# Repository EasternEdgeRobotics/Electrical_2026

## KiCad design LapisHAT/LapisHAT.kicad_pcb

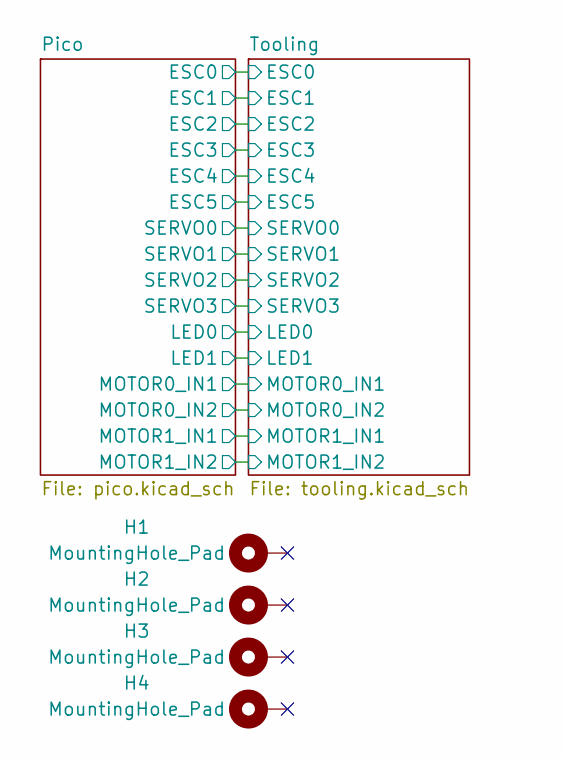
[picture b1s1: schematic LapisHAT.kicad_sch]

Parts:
H1, H2, H3, H4: MountingHole_Pad; MountingHole_3.2mm_M3_Pad_Via

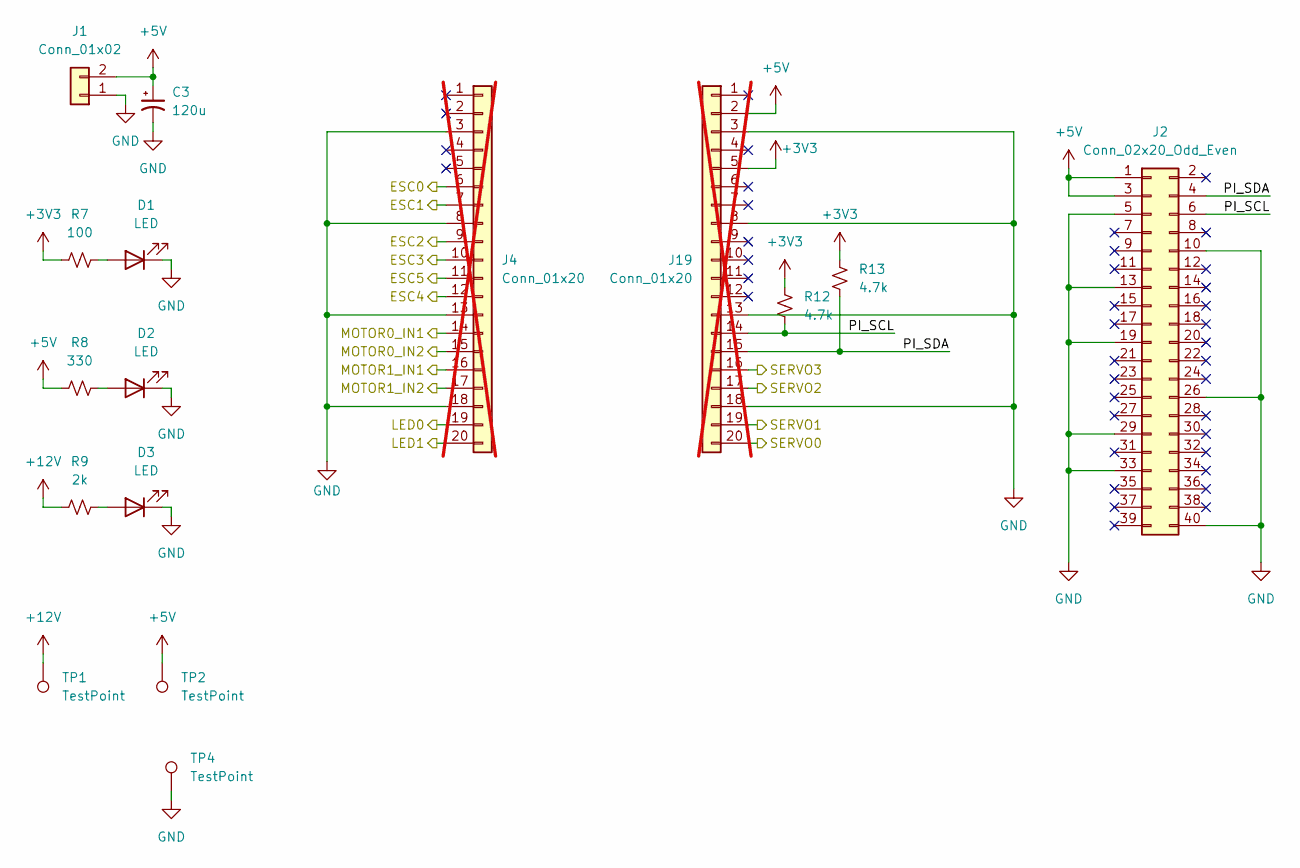
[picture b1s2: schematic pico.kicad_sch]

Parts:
C3: 120u; CP_Elec_10x12.6; LCSC C24725845
D1: LED; LED_0603_1608Metric; LCSC C12065
D2: LED; LED_0603_1608Metric; LCSC C99290
D3: LED; LED_0603_1608Metric; LCSC C94869
J1: Conn_01x02; Molex_Micro-Fit_3.0_43650-0200_1x02_P3.00mm_Horizontal; LCSC C192562
J2: Conn_02x20_Odd_Even; PinHeader_2x20_P2.54mm_Vertical
J4, J19: Conn_01x20; PinHeader_1x20_P2.54mm_Vertical; not fitted
R7: 100; R_0603_1608Metric; LCSC C22775
R8: 330; R_0603_1608Metric; LCSC C23138
R9: 2k; R_0603_1608Metric; LCSC C22975
R12, R13: 4.7k; R_0603_1608Metric; LCSC C23162
TP1, TP2, TP4: TestPoint; TestPoint_Pad_2.0x2.0mm

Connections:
+3V3: J19.5, R7.1, R12.1, R13.1; also elsewhere on the board
+5V: C3.1, J1.2, J2.1, J2.3, J19.2, R8.1, TP2.1; also elsewhere on the board
+12V: R9.1, TP1.1; also elsewhere on the board
/Pico/ESC0: J4.6; also elsewhere on the board
/Pico/ESC1: J4.7; also elsewhere on the board
/Pico/ESC2: J4.9; also elsewhere on the board
/Pico/ESC3: J4.10; also elsewhere on the board
/Pico/ESC4: J4.12; also elsewhere on the board
/Pico/ESC5: J4.11; also elsewhere on the board
/Pico/LED0: J4.19; also elsewhere on the board
/Pico/LED1: J4.20; also elsewhere on the board
/Pico/MOTOR0_IN1: J4.14; also elsewhere on the board
/Pico/MOTOR0_IN2: J4.15; also elsewhere on the board
/Pico/MOTOR1_IN1: J4.16; also elsewhere on the board
/Pico/MOTOR1_IN2: J4.17; also elsewhere on the board
/Pico/PI_SCL: J2.6, J19.14, R12.2
/Pico/PI_SDA: J2.4, J19.15, R13.2
/Pico/SERVO0: J19.20; also elsewhere on the board
/Pico/SERVO1: J19.19; also elsewhere on the board
/Pico/SERVO2: J19.17; also elsewhere on the board
/Pico/SERVO3: J19.16; also elsewhere on the board
GND: C3.2, D1.1 (K), D2.1 (K), D3.1 (K), J1.1, J2.5, J2.10, J2.13, J2.19, J2.26, J2.29, J2.33, J2.40, J4.3, J4.8, J4.13, J4.18, J19.3, J19.8, J19.13, J19.18, TP4.1; also elsewhere on the board
unnamed: D1.2 (A), R7.2
unnamed: D2.2 (A), R8.2
unnamed: D3.2 (A), R9.2

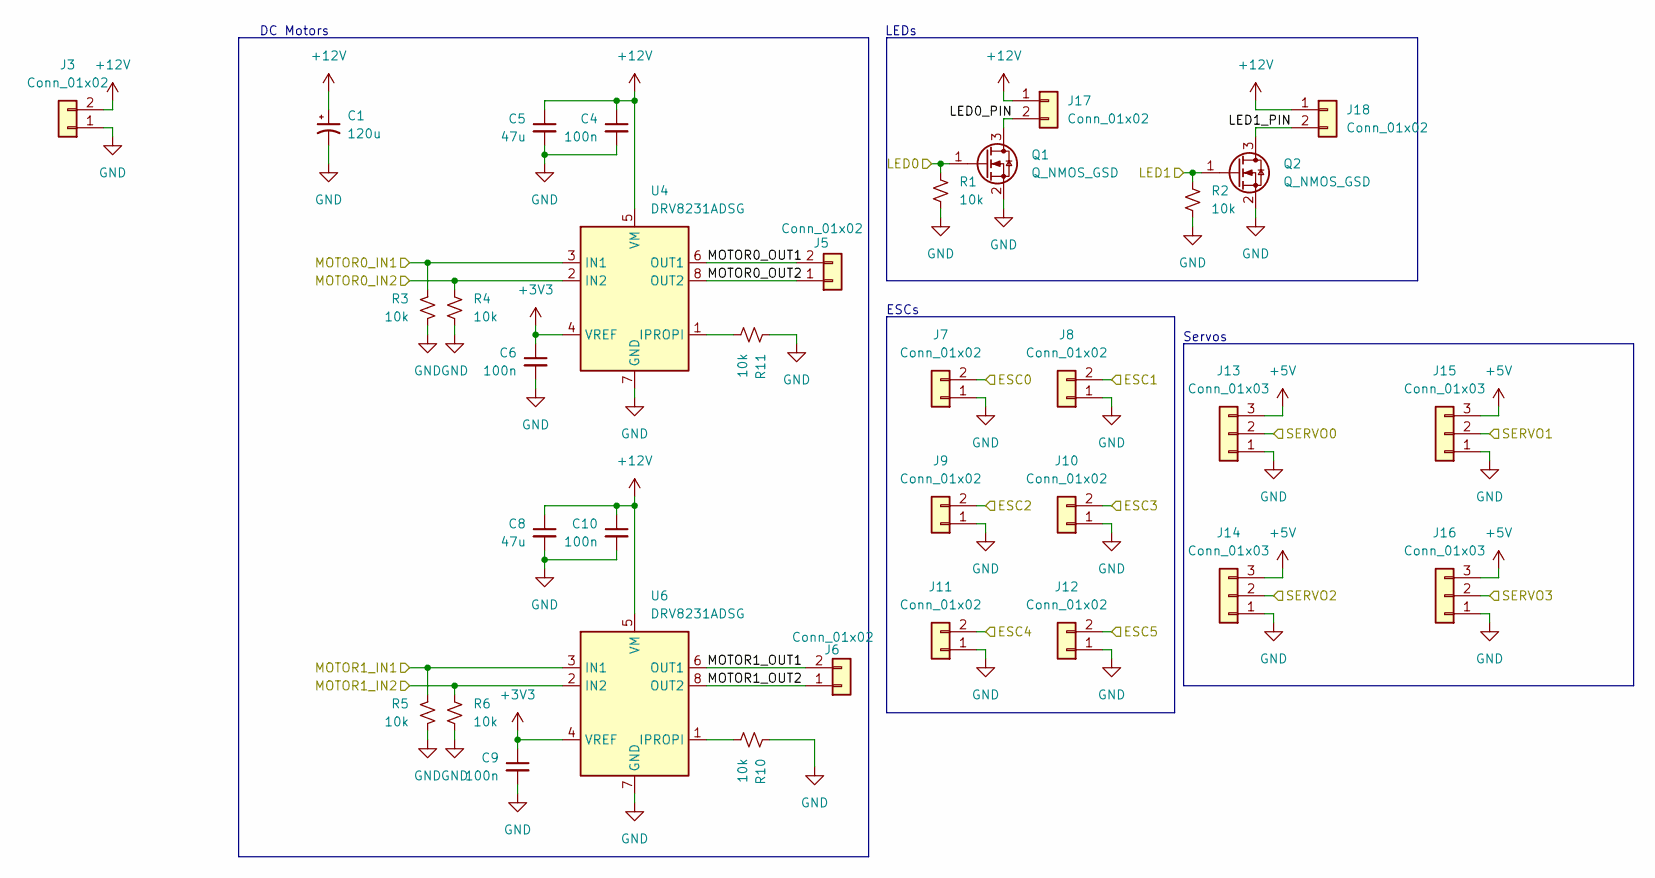
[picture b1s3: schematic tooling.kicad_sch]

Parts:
C1: 120u; CP_Elec_10x12.6; LCSC C24725845
C4, C6, C9, C10: 100n; C_0603_1608Metric; LCSC C14663
C5, C8: 47u; C_1206_3216Metric; LCSC C403725
J3, J5, J6, J17, J18: Conn_01x02; Molex_Micro-Fit_3.0_43650-0200_1x02_P3.00mm_Horizontal; LCSC C192562
J7, J8, J9, J10, J11, J12: Conn_01x02; CONN_70553-xxxx_02_MOL; LCSC C588446
J13, J14, J15, J16: Conn_01x03; Molex_SL_171971-0003_1x03_P2.54mm_Vertical; LCSC C586606
Q1, Q2: Q_NMOS_GSD; SOT-23; LCSC C10488
R1, R2, R3, R4, R5, R6, R10, R11: 10k; R_0603_1608Metric; LCSC C25804
U4, U6: DRV8231ADSG; WSON-8-1EP_2x2mm_P0.5mm_EP0.9x1.6mm; LCSC C5139865

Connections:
+3V3: C6.1, C9.1, U4.4 (VREF), U6.4 (VREF); also elsewhere on the board
+5V: J13.3, J14.3, J15.3, J16.3; also elsewhere on the board
+12V: C1.1, C4.1, C5.1, C8.1, C10.1, J3.2, J17.1, J18.1, U4.5 (VM), U6.5 (VM); also elsewhere on the board
/Pico/ESC0: J7.2; also elsewhere on the board
/Pico/ESC1: J8.2; also elsewhere on the board
/Pico/ESC2: J9.2; also elsewhere on the board
/Pico/ESC3: J10.2; also elsewhere on the board
/Pico/ESC4: J11.2; also elsewhere on the board
/Pico/ESC5: J12.2; also elsewhere on the board
/Pico/LED0: Q1.1 (G), R1.2; also elsewhere on the board
/Pico/LED1: Q2.1 (G), R2.2; also elsewhere on the board
/Pico/MOTOR0_IN1: R3.2, U4.3 (IN1); also elsewhere on the board
/Pico/MOTOR0_IN2: R4.2, U4.2 (IN2); also elsewhere on the board
/Pico/MOTOR1_IN1: R5.2, U6.3 (IN1); also elsewhere on the board
/Pico/MOTOR1_IN2: R6.2, U6.2 (IN2); also elsewhere on the board
/Pico/SERVO0: J13.2; also elsewhere on the board
/Pico/SERVO1: J15.2; also elsewhere on the board
/Pico/SERVO2: J14.2; also elsewhere on the board
/Pico/SERVO3: J16.2; also elsewhere on the board
/Tooling/LED0_PIN: J17.2, Q1.3 (D)
/Tooling/LED1_PIN: J18.2, Q2.3 (D)
/Tooling/MOTOR0_OUT1: J5.2, U4.6 (OUT1)
/Tooling/MOTOR0_OUT2: J5.1, U4.8 (OUT2)
/Tooling/MOTOR1_OUT1: J6.2, U6.6 (OUT1)
/Tooling/MOTOR1_OUT2: J6.1, U6.8 (OUT2)
GND: C1.2, C4.2, C5.2, C6.2, C8.2, C9.2, C10.2, J3.1, J7.1, J8.1, J9.1, J10.1, J11.1, J12.1, J13.1, J14.1, J15.1, J16.1, Q1.2 (S), Q2.2 (S), R1.1, R2.1, R3.1, R4.1, R5.1, R6.1, R10.2, R11.2, U4.7 (GND), U4.9 (GND), U6.7 (GND), U6.9 (GND); also elsewhere on the board
unnamed: R11.1, U4.1 (IPROPI)
unnamed: R10.1, U6.1 (IPROPI)

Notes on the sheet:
DC Motors
LEDs
Servos
ESCs

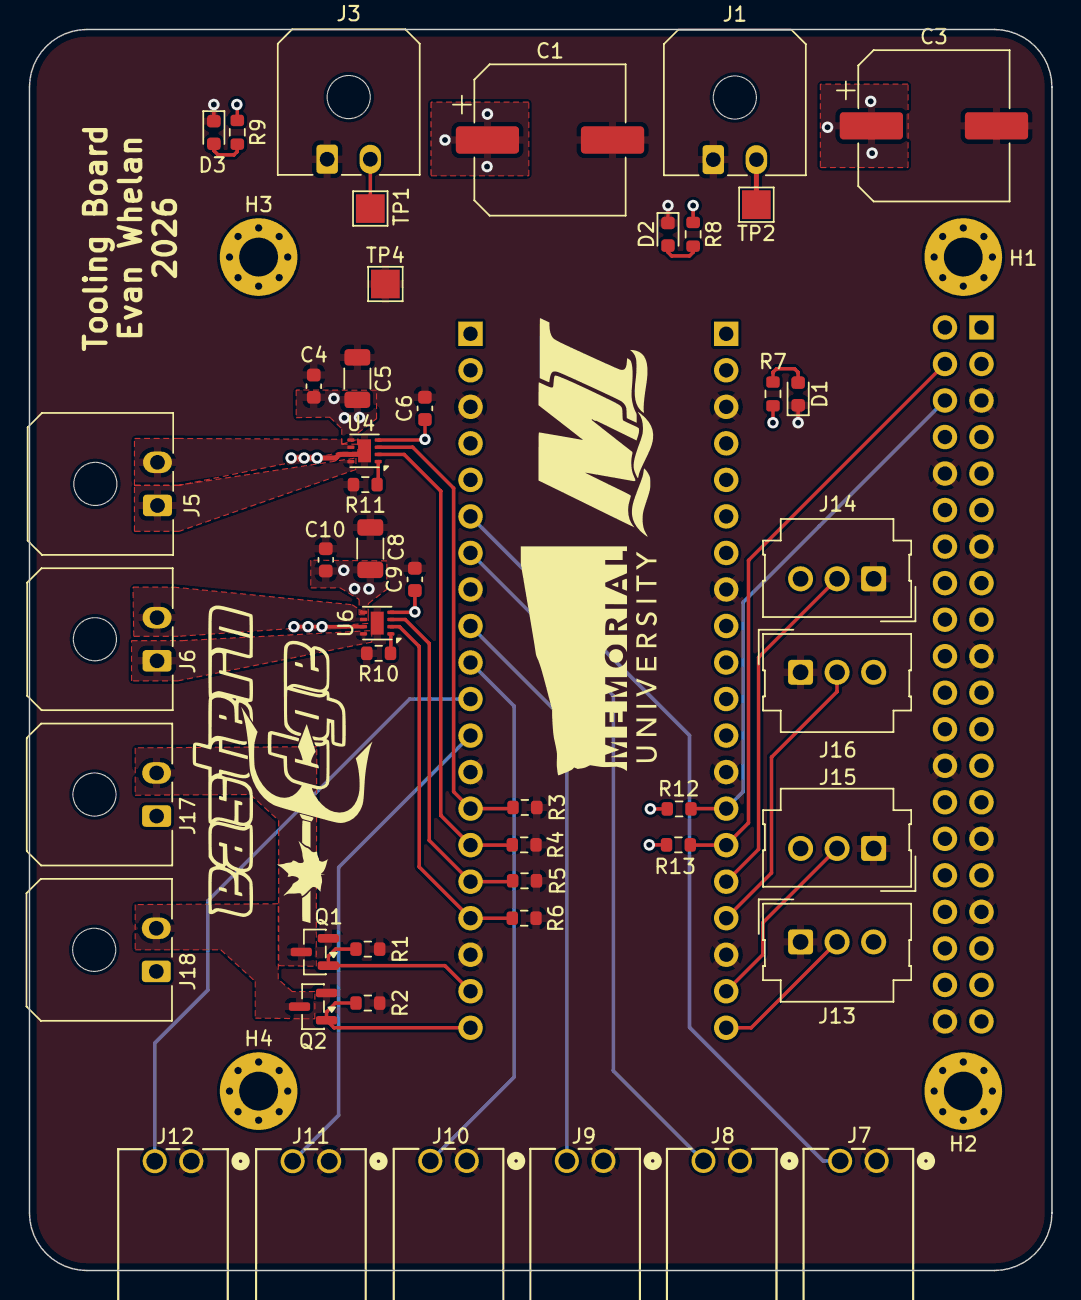
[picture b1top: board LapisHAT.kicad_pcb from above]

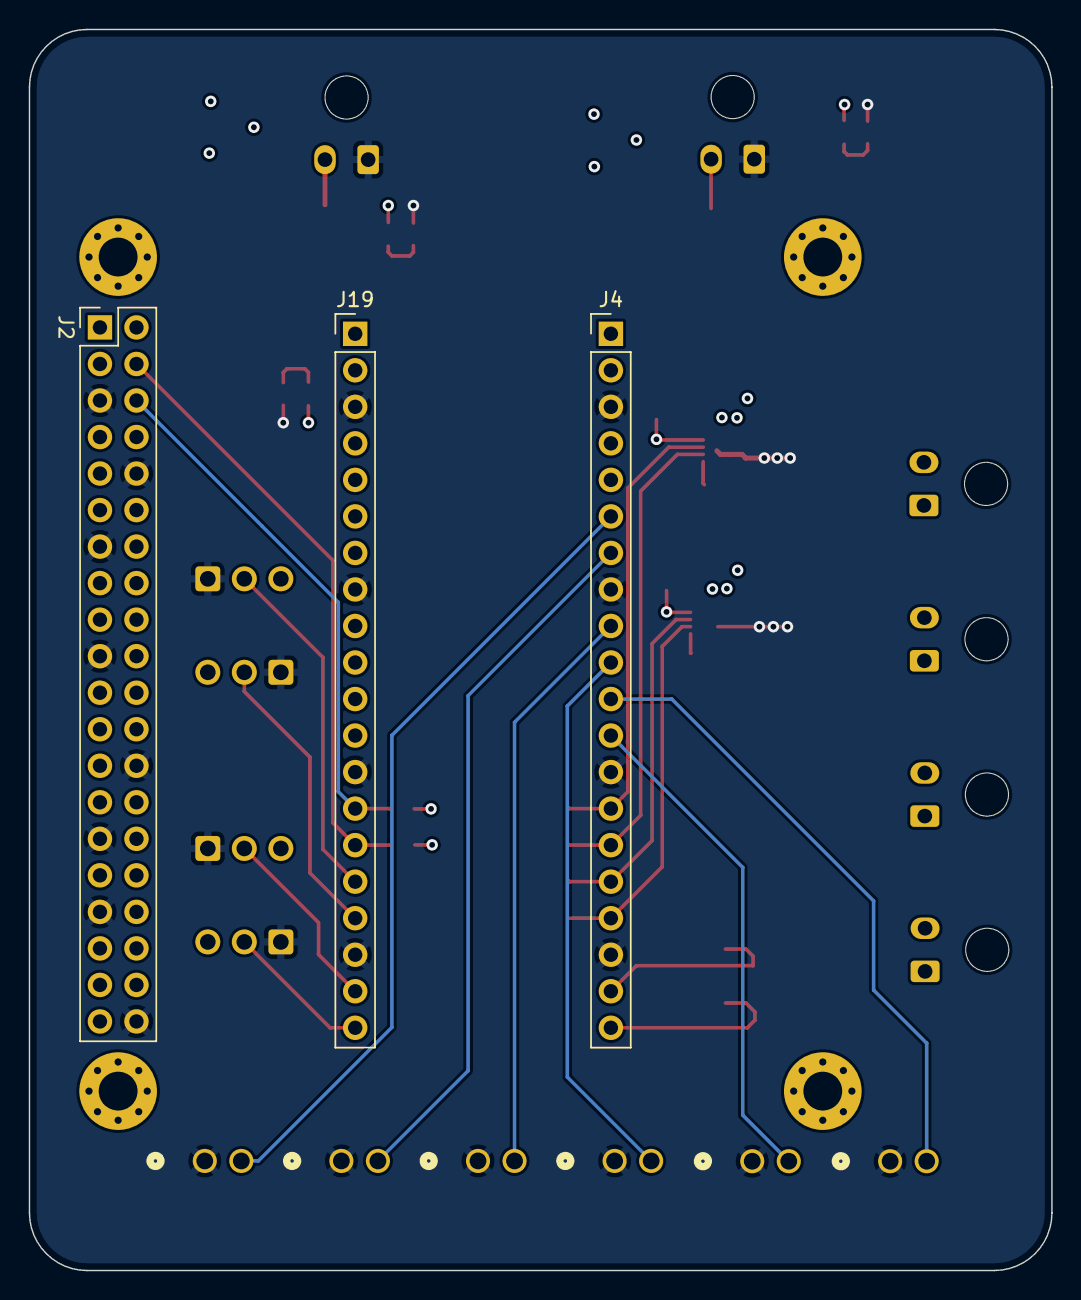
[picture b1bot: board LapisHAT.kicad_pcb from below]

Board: 4 copper layers, 71.1 x 86.3 mm, 54 parts (3 on the bottom side), 33 nets.

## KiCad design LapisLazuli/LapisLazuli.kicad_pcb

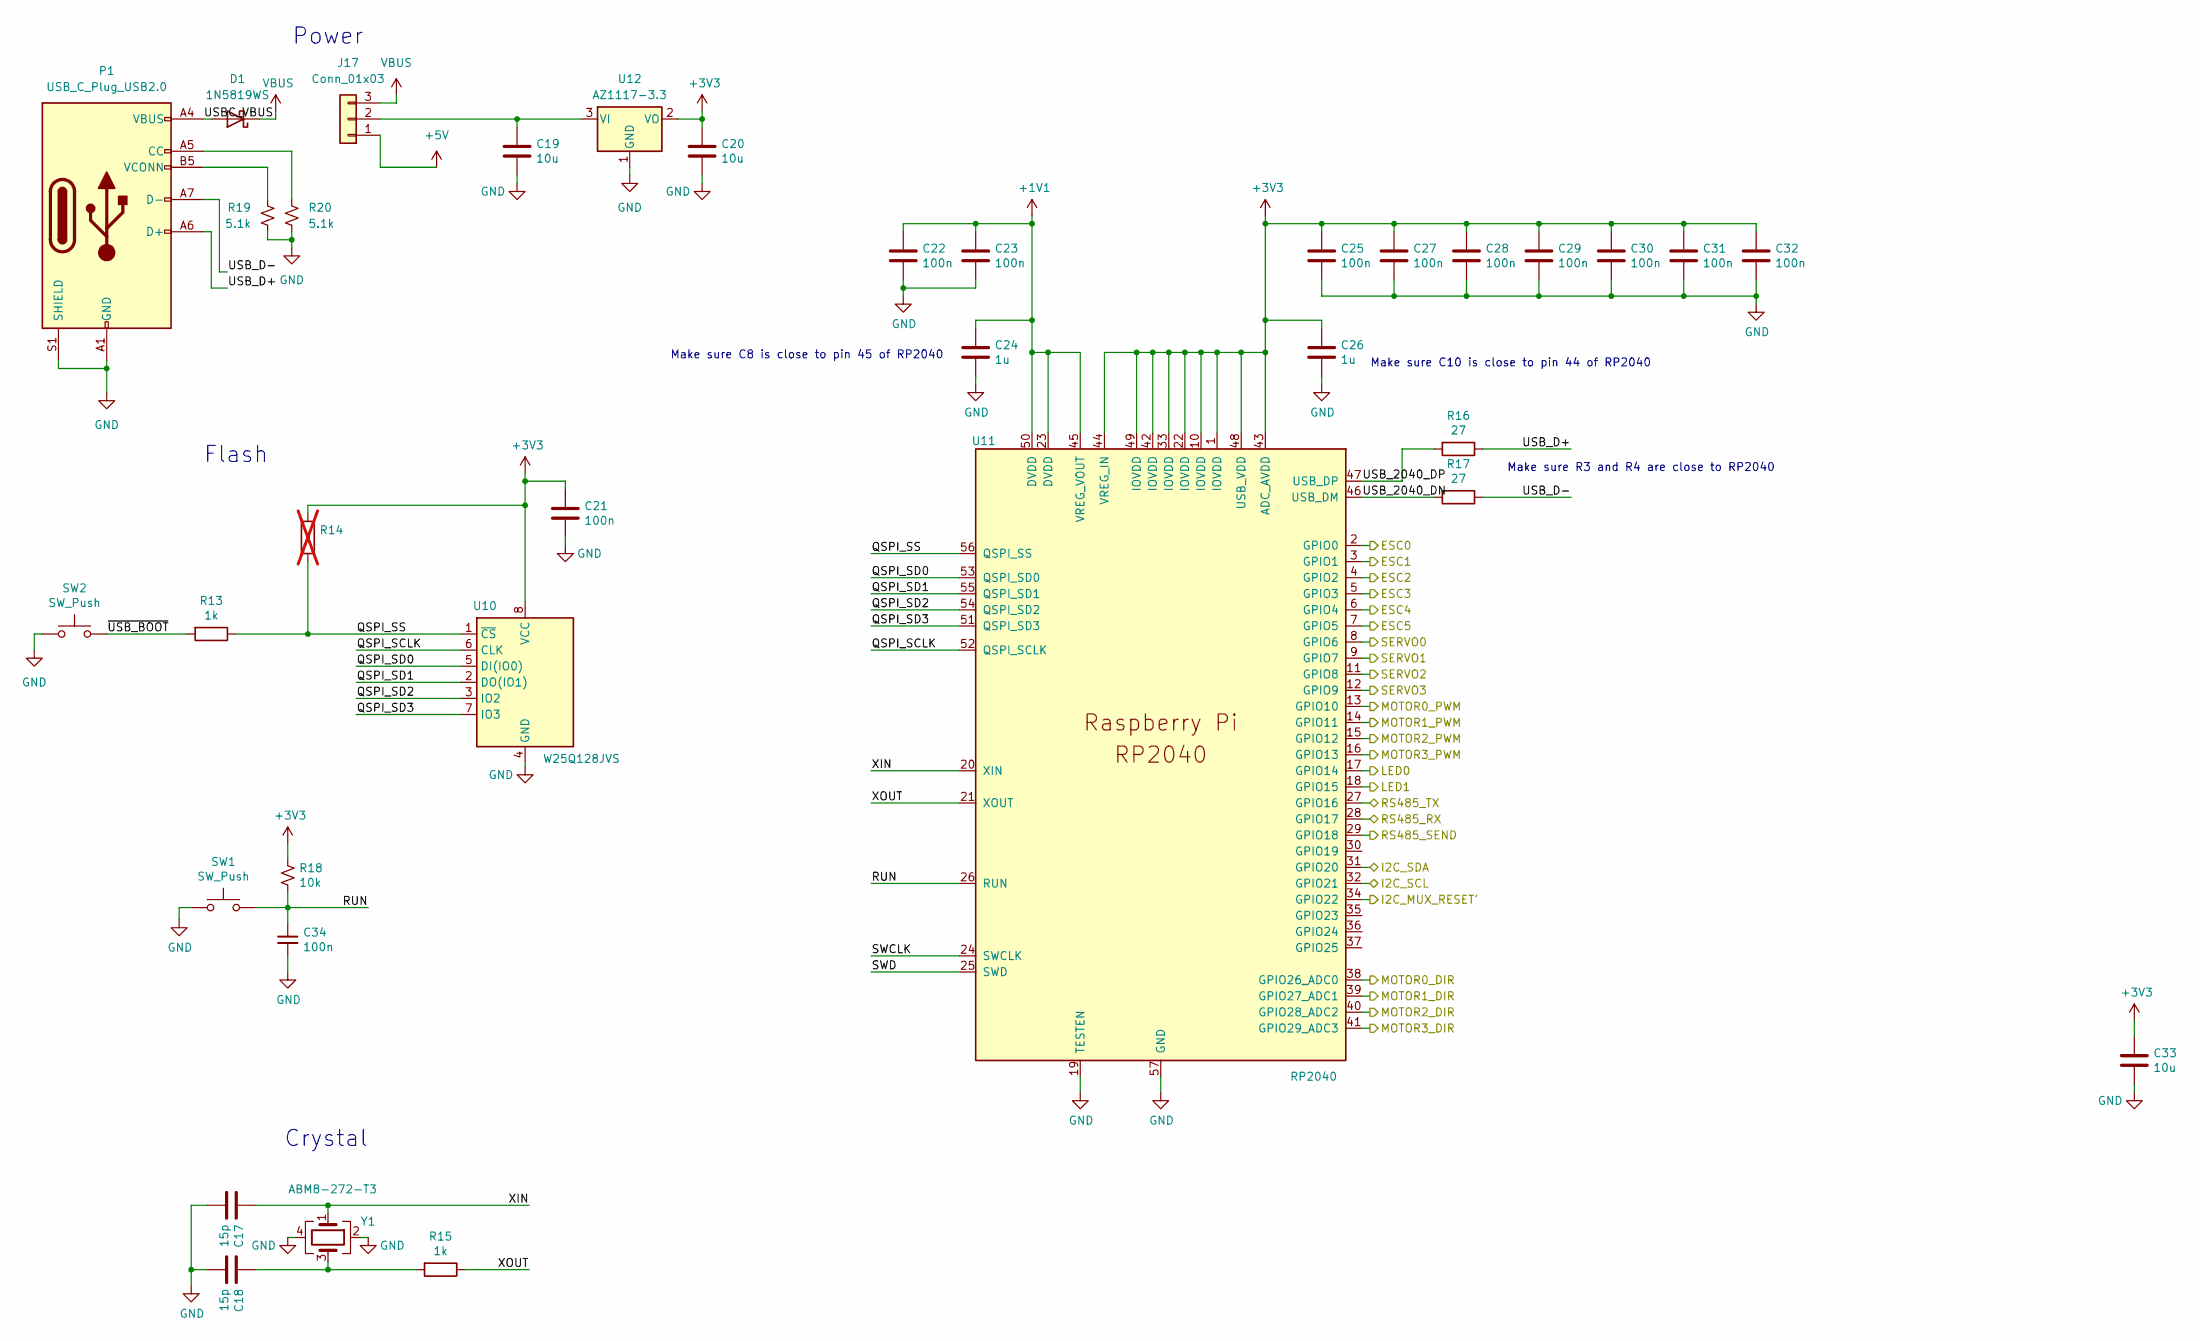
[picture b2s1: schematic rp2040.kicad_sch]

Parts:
C17, C18: 15p; C_0603_1608Metric; LCSC C1644
C19, C20, C33: 10u; C_0805_2012Metric; LCSC C19702
C21, C22, C23, C25, C27, C28, C29, C30, C31, C32, C34: 100n; C_0603_1608Metric; LCSC C14663
C24, C26: 1u; C_0603_1608Metric; LCSC C15849
D1: 1N5819WS; D_SOD-323; LCSC C191023
J17: Conn_01x03; PinHeader_1x03_P2.54mm_Vertical
P1: USB_C_Plug_USB2.0; USB_C_Receptacle_HRO_TYPE-C-31-M-12; LCSC C165948
R13, R15: 1k; R_0603_1608Metric; LCSC C21190
R14: R_0603_1608Metric; not fitted
R16, R17: 27; R_0603_1608Metric; LCSC C25190
R18: 10k; R_0603_1608Metric; LCSC C25804
R19, R20: 5.1k; R_0603_1608Metric; LCSC C23186
SW1, SW2: SW_Push; SW_SPST_EVQPE1; Digikey 401-1707-1-ND
U10: W25Q128JVS; SOIC127P790X216-8N; LCSC C97521
U11: RP2040; RP2040-QFN-56_SMALLER_VIAS; LCSC C2040
U12: AZ1117-3.3; SOT-223-3_TabPin2; LCSC C108495
Y1: ABM8-272-T3; Crystal_SMD_3225-4Pin_3.2x2.5mm; LCSC C20625731

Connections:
+1V1: C22.1, C23.1, C24.1, U11.23 (DVDD), U11.45 (VREG_VOUT), U11.50 (DVDD)
+3V3: C20.1, C21.1, C25.1, C26.1, C27.1, C28.1, C29.1, C30.1, C31.1, C32.1, C33.1, R14.1, R18.1, U10.8 (VCC), U11.1 (IOVDD), U11.10 (IOVDD), U11.22 (IOVDD), U11.33 (IOVDD), U11.42 (IOVDD), U11.43 (ADC_AVDD), U11.44 (VREG_IN), U11.48 (USB_VDD), U11.49 (IOVDD), U12.2 (VO); also elsewhere on the board
+5V: J17.1; also elsewhere on the board
/RP2040/ESC0: U11.2 (GPIO0); also elsewhere on the board
/RP2040/ESC1: U11.3 (GPIO1); also elsewhere on the board
/RP2040/ESC2: U11.4 (GPIO2); also elsewhere on the board
/RP2040/ESC3: U11.5 (GPIO3); also elsewhere on the board
/RP2040/ESC4: U11.6 (GPIO4); also elsewhere on the board
/RP2040/ESC5: U11.7 (GPIO5); also elsewhere on the board
/RP2040/I2C_MUX_RESET': U11.34 (GPIO22); also elsewhere on the board
/RP2040/I2C_SCL: U11.32 (GPIO21); also elsewhere on the board
/RP2040/I2C_SDA: U11.31 (GPIO20); also elsewhere on the board
/RP2040/LED0: U11.17 (GPIO14); also elsewhere on the board
/RP2040/LED1: U11.18 (GPIO15); also elsewhere on the board
/RP2040/MOTOR0_DIR: U11.38 (GPIO26_ADC0); also elsewhere on the board
/RP2040/MOTOR0_PWM: U11.13 (GPIO10); also elsewhere on the board
/RP2040/MOTOR1_DIR: U11.39 (GPIO27_ADC1); also elsewhere on the board
/RP2040/MOTOR1_PWM: U11.14 (GPIO11); also elsewhere on the board
/RP2040/MOTOR2_DIR: U11.40 (GPIO28_ADC2); also elsewhere on the board
/RP2040/MOTOR2_PWM: U11.15 (GPIO12); also elsewhere on the board
/RP2040/MOTOR3_DIR: U11.41 (GPIO29_ADC3); also elsewhere on the board
/RP2040/MOTOR3_PWM: U11.16 (GPIO13); also elsewhere on the board
/RP2040/QSPI_SCLK: U10.6 (CLK), U11.52 (QSPI_SCLK)
/RP2040/QSPI_SD0: U10.5 (DI(IO0)), U11.53 (QSPI_SD0)
/RP2040/QSPI_SD1: U10.2 (DO(IO1)), U11.55 (QSPI_SD1)
/RP2040/QSPI_SD2: U10.3 (IO2), U11.54 (QSPI_SD2)
/RP2040/QSPI_SD3: U10.7 (IO3), U11.51 (QSPI_SD3)
/RP2040/QSPI_SS: R13.1, R14.2, U10.1 (~CS), U11.56 (QSPI_SS)
/RP2040/RS485_RX: U11.28 (GPIO17); also elsewhere on the board
/RP2040/RS485_SEND: U11.29 (GPIO18); also elsewhere on the board
/RP2040/RS485_TX: U11.27 (GPIO16); also elsewhere on the board
/RP2040/RUN: C34.1, R18.2, SW1.2, U11.26 (RUN)
/RP2040/SERVO0: U11.8 (GPIO6); also elsewhere on the board
/RP2040/SERVO1: U11.9 (GPIO7); also elsewhere on the board
/RP2040/SERVO2: U11.11 (GPIO8); also elsewhere on the board
/RP2040/SERVO3: U11.12 (GPIO9); also elsewhere on the board
/RP2040/SWCLK: U11.24 (SWCLK)
/RP2040/SWD: U11.25 (SWD)
/RP2040/USBC_VBUS: D1.2 (A), P1.A4 (VBUS), P1.A9 (VBUS), P1.B4 (VBUS), P1.B9 (VBUS)
/RP2040/USB_2040_DN: R17.2, U11.46 (USB_DM)
/RP2040/USB_2040_DP: R16.2, U11.47 (USB_DP)
/RP2040/USB_D+: P1.A6 (D+), R16.1
/RP2040/USB_D-: P1.A7 (D-), R17.1
/RP2040/XIN: C17.1, U11.20 (XIN), Y1.1
/RP2040/XOUT: R15.1, U11.21 (XOUT)
/RP2040/~USB_BOOT: R13.2, SW2.2
GND: C17.2, C18.2, C19.2, C20.2, C21.2, C22.2, C23.2, C24.2, C25.2, C26.2, C27.2, C28.2, C29.2, C30.2, C31.2, C32.2, C33.2, C34.2, P1.A1 (GND), P1.A12 (GND), P1.B1 (GND), P1.B12 (GND), P1.S1 (SHIELD), R19.2, R20.2, SW1.1, SW2.1, U10.4 (GND), U11.19 (TESTEN), U11.57 (GND), U12.1 (GND), Y1.2, Y1.4; also elsewhere on the board
unnamed: C18.1, R15.2, Y1.3
unnamed: C19.1, J17.2, U12.3 (VI)
unnamed: P1.A5 (CC), R20.1
unnamed: P1.B5 (VCONN), R19.1
VBUS: D1.1 (K), J17.3

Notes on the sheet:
Make sure C10 is close to pin 44 of RP2040
Make sure R3 and R4 are close to RP2040
Make sure C8 is close to pin 45 of RP2040
Power
Crystal
Flash

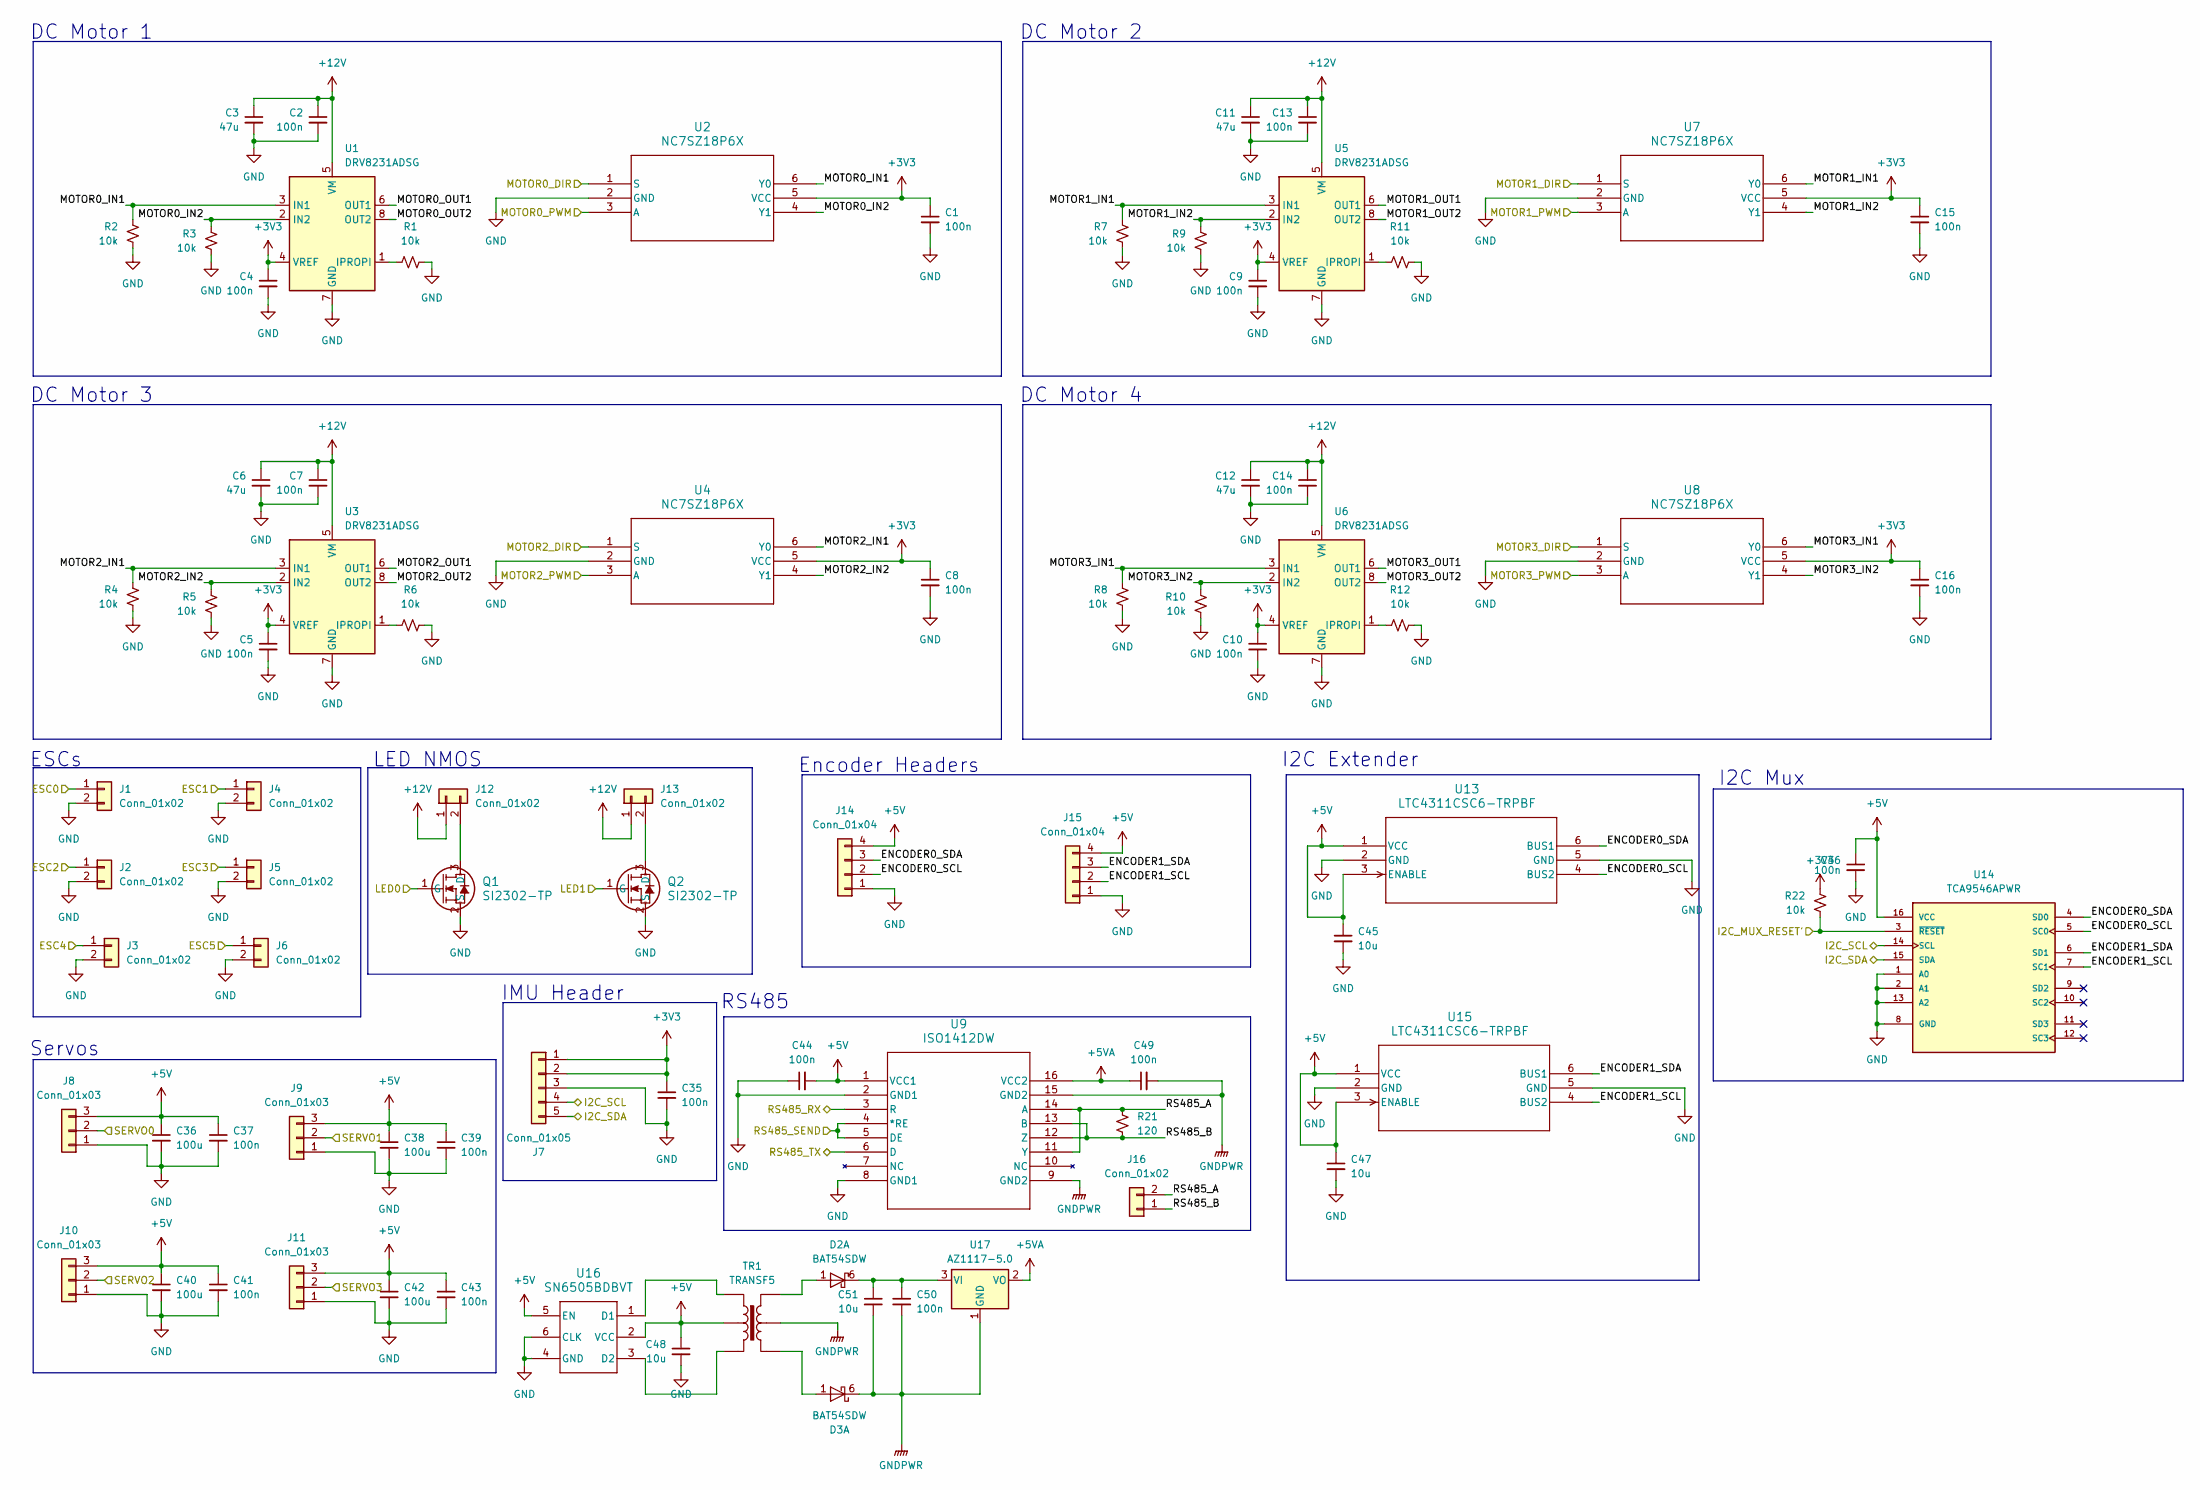
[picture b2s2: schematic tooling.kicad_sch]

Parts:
C1, C2, C4, C5, C7, C8, C9, C10, C13, C14, C15, C16, C35, C37, C39, C41, C43, C44, C46, C49, C50: 100n; C_0603_1608Metric; LCSC C14663
C3, C6, C11, C12: 47u; C_0805_2012Metric; LCSC C16780
C36, C38, C40, C42: 100u; CP_Elec_6.3x7.7; LCSC C3338
C45, C47, C48, C51: 10u; C_0805_2012Metric; LCSC C19702
D2, D3: BAT54SDW; SOT-363_SC-70-6; LCSC C77323
J1, J2, J3, J4, J5, J6, J12, J13, J16: Conn_01x02; PinHeader_1x02_P2.54mm_Vertical
J7: Conn_01x05; PinHeader_1x05_P2.54mm_Vertical
J8, J9, J10, J11: Conn_01x03; PinHeader_1x03_P2.54mm_Vertical
J14, J15: Conn_01x04; PinHeader_1x04_P2.54mm_Vertical
Q1, Q2: SI2302-TP; SOT-23; LCSC C10488
R1, R2, R3, R4, R5, R6, R7, R8, R9, R10, R11, R12, R22: 10k; R_0603_1608Metric; LCSC C25804
R21: 120; R_0603_1608Metric; LCSC C22787
TR1: TRANSF5; WE-PPTI_1006_L10.2W6.73H4.19; LCSC C2802211
U1, U3, U5, U6: DRV8231ADSG; WSON-8-1EP_2x2mm_P0.5mm_EP0.9x1.6mm; LCSC C5139865
U2, U4, U7, U8: NC7SZ18P6X; SOT-363_SC-70-6; LCSC C462890
U9: ISO1412DW; SOIC-16W_7.5x10.3mm_P1.27mm; LCSC C2672327
U13, U15: LTC4311CSC6-TRPBF; SOT-363_SC-70-6; LCSC C580856
U14: TCA9546APWR; TSSOP-16_4.4x5mm_P0.65mm; PARTREV B; LCSC C201653
U16: SN6505BDBVT; SOT-23-6; LCSC C2156022
U17: AZ1117-5.0; SOT-223-3_TabPin2; LCSC C526405

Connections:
+3V3: C1.1, C4.1, C5.1, C8.1, C9.1, C10.1, C15.1, C16.1, C35.1, J7.1, J7.2, R22.1, U1.4 (VREF), U2.5 (VCC), U3.4 (VREF), U4.5 (VCC), U5.4 (VREF), U6.4 (VREF), U7.5 (VCC), U8.5 (VCC); also elsewhere on the board
+5V: C36.1, C37.1, C38.1, C39.1, C40.1, C41.1, C42.1, C43.1, C44.2, C45.1, C46.1, C47.1, C48.1, J8.3, J9.3, J10.3, J11.3, J14.4, J15.4, TR1.2, U9.1 (VCC1), U13.1 (VCC), U13.3 (ENABLE), U14.16 (VCC), U15.1 (VCC), U15.3 (ENABLE), U16.2 (VCC), U16.5 (EN); also elsewhere on the board
+5VA: C49.1, U9.16 (VCC2), U17.2 (VO)
+12V: C2.1, C3.1, C6.1, C7.1, C11.1, C12.1, C13.1, C14.1, J12.1, J13.1, U1.5 (VM), U3.5 (VM), U5.5 (VM), U6.5 (VM)
/RP2040/ESC0: J1.1; also elsewhere on the board
/RP2040/ESC1: J4.1; also elsewhere on the board
/RP2040/ESC2: J2.1; also elsewhere on the board
/RP2040/ESC3: J5.1; also elsewhere on the board
/RP2040/ESC4: J3.1; also elsewhere on the board
/RP2040/ESC5: J6.1; also elsewhere on the board
/RP2040/I2C_MUX_RESET': R22.2, U14.3 (~RESET); also elsewhere on the board
/RP2040/I2C_SCL: J7.4, U14.14 (SCL); also elsewhere on the board
/RP2040/I2C_SDA: J7.5, U14.15 (SDA); also elsewhere on the board
/RP2040/LED0: Q1.1 (G); also elsewhere on the board
/RP2040/LED1: Q2.1 (G); also elsewhere on the board
/RP2040/MOTOR0_DIR: U2.1 (S); also elsewhere on the board
/RP2040/MOTOR0_PWM: U2.3 (A); also elsewhere on the board
/RP2040/MOTOR1_DIR: U7.1 (S); also elsewhere on the board
/RP2040/MOTOR1_PWM: U7.3 (A); also elsewhere on the board
/RP2040/MOTOR2_DIR: U4.1 (S); also elsewhere on the board
/RP2040/MOTOR2_PWM: U4.3 (A); also elsewhere on the board
/RP2040/MOTOR3_DIR: U8.1 (S); also elsewhere on the board
/RP2040/MOTOR3_PWM: U8.3 (A); also elsewhere on the board
/RP2040/RS485_RX: U9.3 (R); also elsewhere on the board
/RP2040/RS485_SEND: U9.4 (*RE), U9.5 (DE); also elsewhere on the board
/RP2040/RS485_TX: U9.6 (D); also elsewhere on the board
/RP2040/SERVO0: J8.2; also elsewhere on the board
/RP2040/SERVO1: J9.2; also elsewhere on the board
/RP2040/SERVO2: J10.2; also elsewhere on the board
/RP2040/SERVO3: J11.2; also elsewhere on the board
/Tooling/ENCODER0_SCL: J14.2, U13.4 (BUS2), U14.5 (SC0)
/Tooling/ENCODER0_SDA: J14.3, U13.6 (BUS1), U14.4 (SD0)
/Tooling/ENCODER1_SCL: J15.2, U14.7 (SC1), U15.4 (BUS2)
/Tooling/ENCODER1_SDA: J15.3, U14.6 (SD1), U15.6 (BUS1)
/Tooling/MOTOR0_IN1: R2.1, U1.3 (IN1), U2.6 (Y0)
/Tooling/MOTOR0_IN2: R3.1, U1.2 (IN2), U2.4 (Y1)
/Tooling/MOTOR0_OUT1: U1.6 (OUT1)
/Tooling/MOTOR0_OUT2: U1.8 (OUT2)
/Tooling/MOTOR1_IN1: R7.1, U5.3 (IN1), U7.6 (Y0)
/Tooling/MOTOR1_IN2: R9.1, U5.2 (IN2), U7.4 (Y1)
/Tooling/MOTOR1_OUT1: U5.6 (OUT1)
/Tooling/MOTOR1_OUT2: U5.8 (OUT2)
/Tooling/MOTOR2_IN1: R4.1, U3.3 (IN1), U4.6 (Y0)
/Tooling/MOTOR2_IN2: R5.1, U3.2 (IN2), U4.4 (Y1)
/Tooling/MOTOR2_OUT1: U3.6 (OUT1)
/Tooling/MOTOR2_OUT2: U3.8 (OUT2)
/Tooling/MOTOR3_IN1: R8.1, U6.3 (IN1), U8.6 (Y0)
/Tooling/MOTOR3_IN2: R10.1, U6.2 (IN2), U8.4 (Y1)
/Tooling/MOTOR3_OUT1: U6.6 (OUT1)
/Tooling/MOTOR3_OUT2: U6.8 (OUT2)
/Tooling/RS485_A: J16.2, R21.1, U9.11 (Y), U9.14 (A)
/Tooling/RS485_B: J16.1, R21.2, U9.12 (Z), U9.13 (B)
GND: C1.2, C2.2, C3.2, C4.2, C5.2, C6.2, C7.2, C8.2, C9.2, C10.2, C11.2, C12.2, C13.2, C14.2, C15.2, C16.2, C35.2, C36.2, C37.2, C38.2, C39.2, C40.2, C41.2, C42.2, C43.2, C44.1, C45.2, C46.2, C47.2, C48.2, J1.2, J2.2, J3.2, J4.2, J5.2, J6.2, J7.3, J8.1, J9.1, J10.1, J11.1, J14.1, J15.1, Q1.2 (S), Q2.2 (S), R1.2, R2.2, R3.2, R4.2, R5.2, R6.2, R7.2, R8.2, R9.2, R10.2, R11.2, R12.2, U1.7 (GND), U1.9 (GND), U2.2 (GND), U3.7 (GND), U3.9 (GND), U4.2 (GND), U5.7 (GND), U5.9 (GND), U6.7 (GND), U6.9 (GND), U7.2 (GND), U8.2 (GND), U9.2 (GND1), U9.8 (GND1), U13.2 (GND), U13.5 (GND), U14.1 (A0), U14.2 (A1), U14.8 (GND), U14.13 (A2), U15.2 (GND), U15.5 (GND), U16.4 (GND), U16.6 (CLK); also elsewhere on the board
GNDPWR: C49.2, C50.2, C51.2, D3.6 (K), TR1.5, U9.9 (GND2), U9.15 (GND2), U17.1 (GND)
unnamed: D2.1 (A), TR1.6
unnamed: C50.1, C51.1, D2.6 (K), U17.3 (VI)
unnamed: D3.1 (A), TR1.4
unnamed: J12.2, Q1.3 (D)
unnamed: J13.2, Q2.3 (D)
unnamed: R1.1, U1.1 (IPROPI)
unnamed: R6.1, U3.1 (IPROPI)
unnamed: R11.1, U5.1 (IPROPI)
unnamed: R12.1, U6.1 (IPROPI)
unnamed: TR1.1, U16.1 (D1)
unnamed: TR1.3, U16.3 (D2)

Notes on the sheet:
Servos
RS485
DC Motor 3
LED NMOS
ESCs
IMU Header
Encoder Headers
DC Motor 2
I2C Extender
I2C Mux
DC Motor 4
DC Motor 1

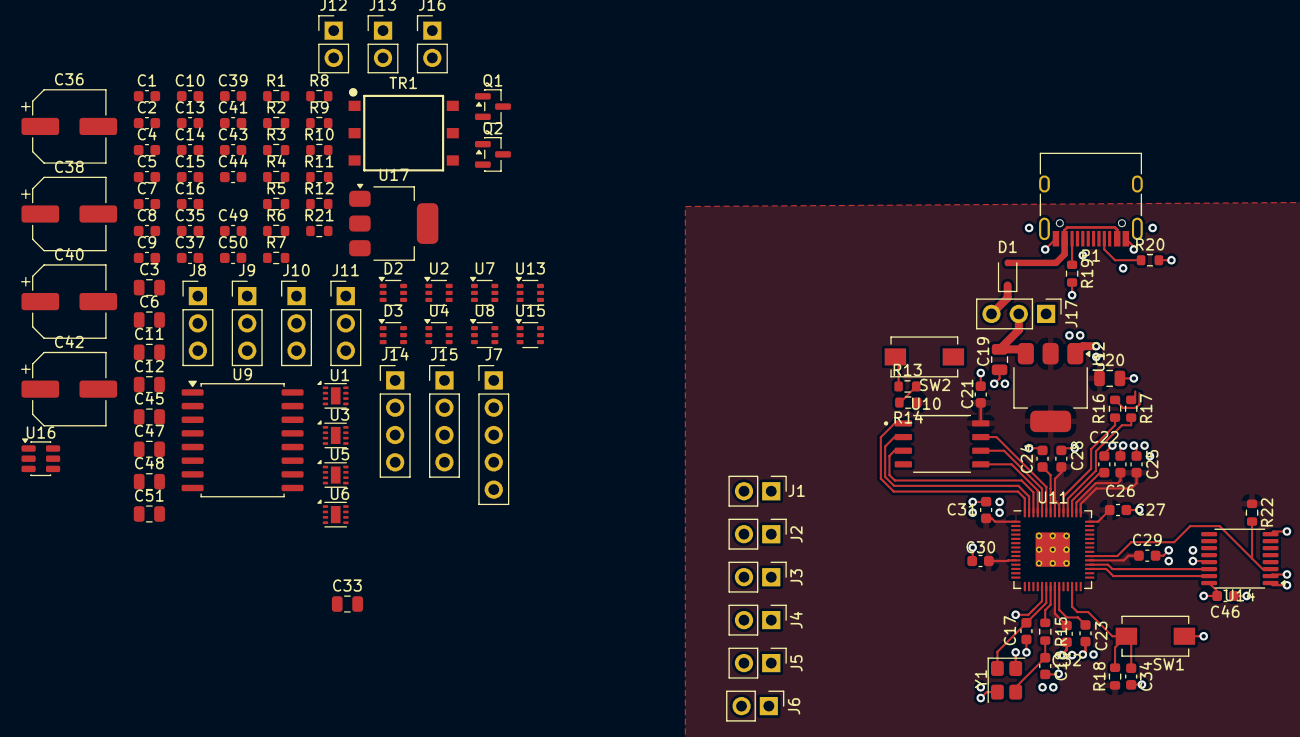
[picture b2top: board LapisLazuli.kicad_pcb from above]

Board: 4 copper layers, 117 parts (0 on the bottom side), 78 nets.
